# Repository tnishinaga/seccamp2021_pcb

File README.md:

# ft2232_jtag_tap

# KiCad version

5.1.8

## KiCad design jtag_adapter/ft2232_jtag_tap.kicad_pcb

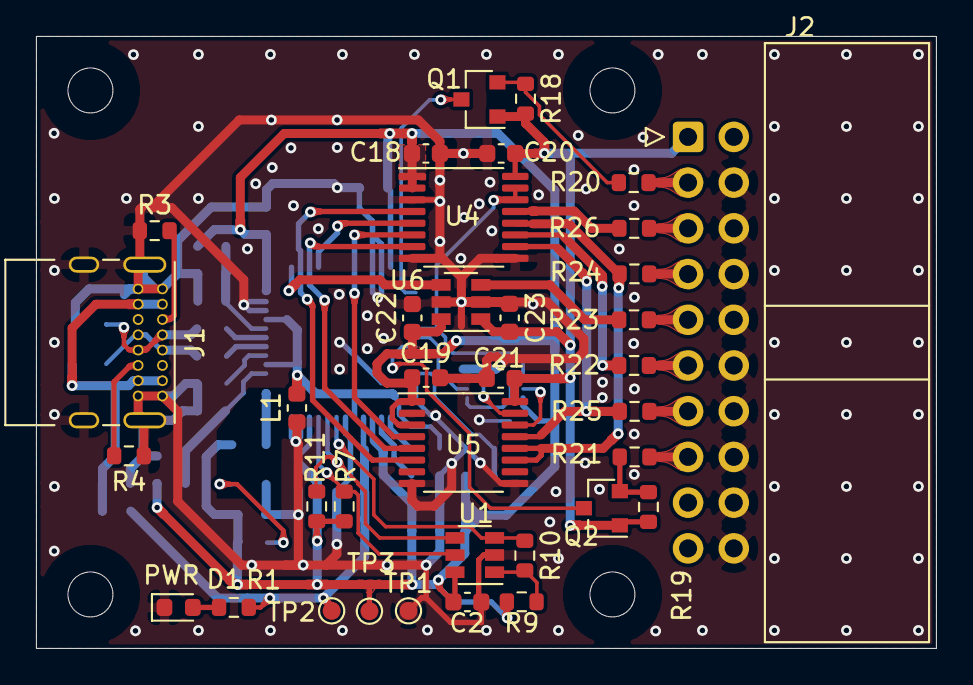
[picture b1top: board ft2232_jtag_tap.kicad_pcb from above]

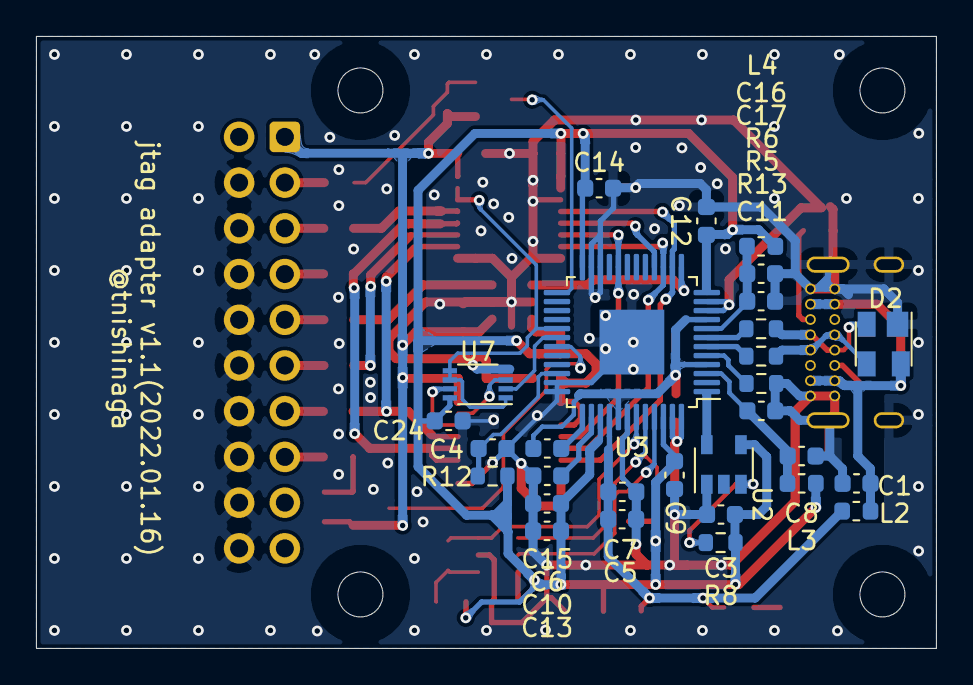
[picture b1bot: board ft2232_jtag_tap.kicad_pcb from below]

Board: 2 copper layers, 50.0 x 34.0 mm, 69 parts (29 on the bottom side), 50 nets.

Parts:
C1: 0.01uF; C_0603_1608Metric
C2: N.F./0.1uF; C_0603_1608Metric
C3, C4, C6, C7, C9, C11, C12, C13, C14, C15, C17, C18, C19, C20, C21, C22, C23, C24: 0.1uF; C_0603_1608Metric
C5, C8, C10, C16: 4.7uF; C_0603_1608Metric
D1: PWR_LED; LED_0603_1608Metric
D2: PRTR5V0U2X; SOT-143
H1, H2, H3, H4: MountingHole; MountingHole_2.5mm
J1: USB_C_Receptacle_USB2.0; USB_C_Receptacle_GCT_USB4085
J2: Conn_ARM_JTAG_SWD_20; IDC-Header_2x10_P2.54mm_Horizontal
L1, L2, L3, L4: 600R/0.5A; L_0603_1608Metric
Q1, Q2: BSS138; SOT-23
R1: 1k; R_0603_1608Metric
R3, R4: 5.1k; R_0603_1608Metric
R5, R6, R20, R21, R22, R23, R24, R25, R26: 0; R_0603_1608Metric
R7, R9, R11: N.F./10k; R_0603_1608Metric
R8, R18, R19: 10k; R_0603_1608Metric
R10: N.F./2k; R_0603_1608Metric
R12: 100k; R_0603_1608Metric
R13: 12k/1%; R_0603_1608Metric
TP1: GND; TestPoint_Pad_D1.0mm
TP2: +5V; TestPoint_Pad_D1.0mm
TP3: +3.3V; TestPoint_Pad_D1.0mm
U1: N.F./93AA56BT-I/OT; SOT-23-6
U2: SIT2001B; SOT-23-5
U3: FT232HL; LQFP-48-1EP_7x7mm_P0.5mm_EP3.6x3.6mm
U4, U5: SN74AXCH4T245PW; TSSOP-16_4.4x5mm_P0.65mm
U6: SN74AXCH1T45DBVR; SOT-23-6
U7: SN74LVC2G00DCUT; VSSOP-8_2.3x2mm_P0.5mm

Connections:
+1V8: C6.1, U3.38
+3V3: C2.1, C3.1, C9.1, C10.1, C12.1, C13.1, C14.1, C18.1, C19.1, C22.1, C24.2, L3.2, L4.2, R7.2, R8.2, R9.2, R11.2, R12.2, TP3.1, U1.6, U2.4, U3.12, U3.24, U3.39, U3.46, U4.1, U4.2, U5.1, U5.3, U6.6, U7.8
+5V: C5.1, C7.1, L2.1, R1.2, TP2.1, U3.40
/ft232hl/EEPROM_CLK: R11.1, U1.4, U3.44
/ft232hl/EEPROM_CS: R7.1, U1.5, U3.45
/ft232hl/EEPROM_DATA: R10.1, U1.3, U3.43
/ft232hl/JTAG_RTCK: U3.20, U4.6, U5.4
/ft232hl/JTAG_TCK: U3.13, U6.4
/ft232hl/JTAG_TDI: U3.14, U4.4, U5.6
/ft232hl/JTAG_TDO: U3.15, U4.7, U5.5
/ft232hl/JTAG_TMS: U3.16, U4.5
/ft232hl/JTAG_nSRST: Q2.3, U3.31
/ft232hl/JTAG_nTRST: Q1.3, U3.25
/ft232hl/SWDIO_OE: U3.30, U7.2
/ft232hl/SWD_EN: U3.29, U4.14, U4.15, U7.1, U7.5, U7.6
/ft232hl/USB_D+: R6.1, U3.7
/ft232hl/USB_D-: R5.1, U3.6
/ft232hl/VCCA: C15.1, U3.37
/ft232hl/VPHY: C8.1, C11.1, L3.1, U3.3
/ft232hl/VPLL: C16.1, C17.1, L4.1, U3.8
/ft232hl/XCSI: U2.5, U3.1
/ft232hl/~RESET: C4.1, R12.1, U3.34
/jtag/CONN_RTCK: J2.11, R22.2
/jtag/CONN_TCK: J2.9, R23.2
/jtag/CONN_TDI: J2.5, R26.2
/jtag/CONN_TDO: J2.13, R25.2
/jtag/CONN_TMS: J2.7, R24.2
/jtag/CONN_~SRST: J2.15, R21.2
/jtag/CONN_~TRST: J2.3, R20.2
/jtag/RTCK: R22.1, U4.11
/jtag/TCK_SWDCLK: R23.1, U6.3
/jtag/TDI: R26.1, U4.13
/jtag/TDO_SWO: R25.1, U4.10, U5.13
/jtag/TMS_SWDIO: R24.1, U4.12, U5.11, U5.12
/jtag/VTREF: C20.2, C21.2, C23.2, J2.1, Q1.1, Q2.1, R18.2, R19.2, U4.16, U5.16, U6.1
/jtag/~SRST: Q2.2, R19.1, R21.1
/jtag/~SWD_EN: U5.15, U7.3
/jtag/~SWD_OE: U5.14, U7.7
/jtag/~TRST: Q1.2, R18.1, R20.1
/usb/D+: D2.2, J1.A6, J1.B6, R6.2
/usb/D-: D2.3, J1.A7, J1.B7, R5.2
/usb/VBUS: C1.1, D2.4, J1.A4, J1.A9, J1.B4, J1.B9, L2.2
GND: C1.2, C2.2, C3.2, C4.2, C5.2, C6.2, C7.2, C8.2, C9.2, C10.2, C11.2, C12.2, C13.2, C14.2, C16.2, C17.2, C18.2, C19.2, C20.1, C21.1, C22.2, C23.1, C24.1, D1.1, D2.1, J1.A1, J1.A12, J1.B1, J1.B12, J1.S1, J2.4, J2.6, J2.8, J2.10, J2.12, J2.14, J2.16, J2.18, J2.20, L1.1, R3.1, R4.1, R13.2, TP1.1, U1.2, U2.1, U3.10, U3.11, U3.22, U3.23, U3.35, U3.36, U3.42, U3.47, U3.48, U3.49, U4.3, U4.8, U4.9, U5.2, U5.8, U5.9, U6.2, U6.5, U7.4
GNDA: C15.2, L1.2, U3.4, U3.9, U3.41
unnamed: D1.2, R1.1
unnamed: J1.A5, R3.2
unnamed: J1.B5, R4.2
unnamed: R8.1, U2.3
unnamed: R9.1, R10.2, U1.1
unnamed: R13.1, U3.5

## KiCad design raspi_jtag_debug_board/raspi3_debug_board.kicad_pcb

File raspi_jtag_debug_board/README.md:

# raspi_development_expand_board
Development board that expands JTAG, UART, I2C, PWM ports for Raspberry Pi

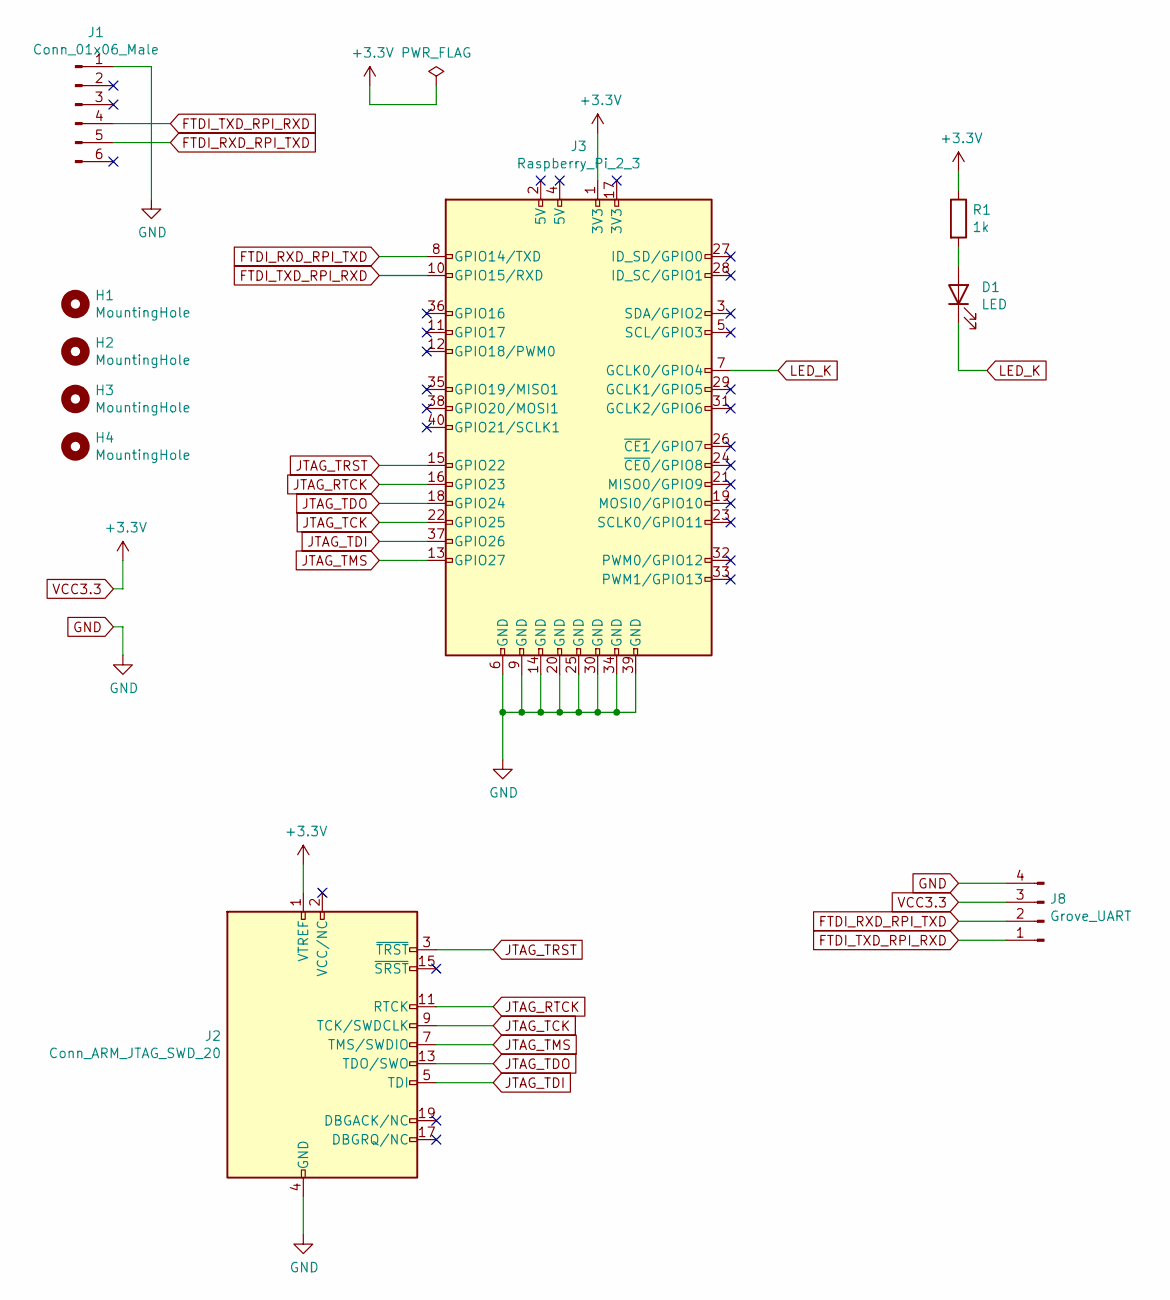
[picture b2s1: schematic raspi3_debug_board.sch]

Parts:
D1: LED; LED_D3.0mm
H1, H2, H3, H4: MountingHole; MountingHole_2.7mm_M2.5
J1: Conn_01x06_Male; PinHeader_1x06_P2.54mm_Horizontal
J2: Conn_ARM_JTAG_SWD_20; Multicomp_MC9A22-2034_2x10_P2.54mm_Horizontal
J3: Raspberry_Pi_2_3; PinSocket_2x20_P2.54mm_Vertical
J8: Grove_UART; NS-Tech_Grove_1x04_P2mm_Vertical
R1: 1k; R_Axial_DIN0207_L6.3mm_D2.5mm_P10.16mm_Horizontal

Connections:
FTDI_RXD_RPI_TXD: J1.5, J3.8 (GPIO14/TXD), J8.2
FTDI_TXD_RPI_RXD: J1.4, J3.10 (GPIO15/RXD), J8.1
GND: J1.1, J2.4 (GND), J2.6 (GND), J2.8 (GND), J2.10 (GND), J2.12 (GND), J2.14 (GND), J2.16 (GND), J2.18 (GND), J2.20 (GND), J3.6 (GND), J3.9 (GND), J3.14 (GND), J3.20 (GND), J3.25 (GND), J3.30 (GND), J3.34 (GND), J3.39 (GND), J8.4
JTAG_RTCK: J2.11 (RTCK), J3.16 (GPIO23)
JTAG_TCK: J2.9 (TCK/SWDCLK), J3.22 (GPIO25)
JTAG_TDI: J2.5 (TDI), J3.37 (GPIO26)
JTAG_TDO: J2.13 (TDO/SWO), J3.18 (GPIO24)
JTAG_TMS: J2.7 (TMS/SWDIO), J3.13 (GPIO27)
JTAG_TRST: J2.3 (~TRST~), J3.15 (GPIO22)
LED_K: D1.1 (K), J3.7 (GCLK0/GPIO4)
unnamed: D1.2 (A), R1.2
VCC3.3: J2.1 (VTREF), J3.1 (3V3), J8.3, R1.1

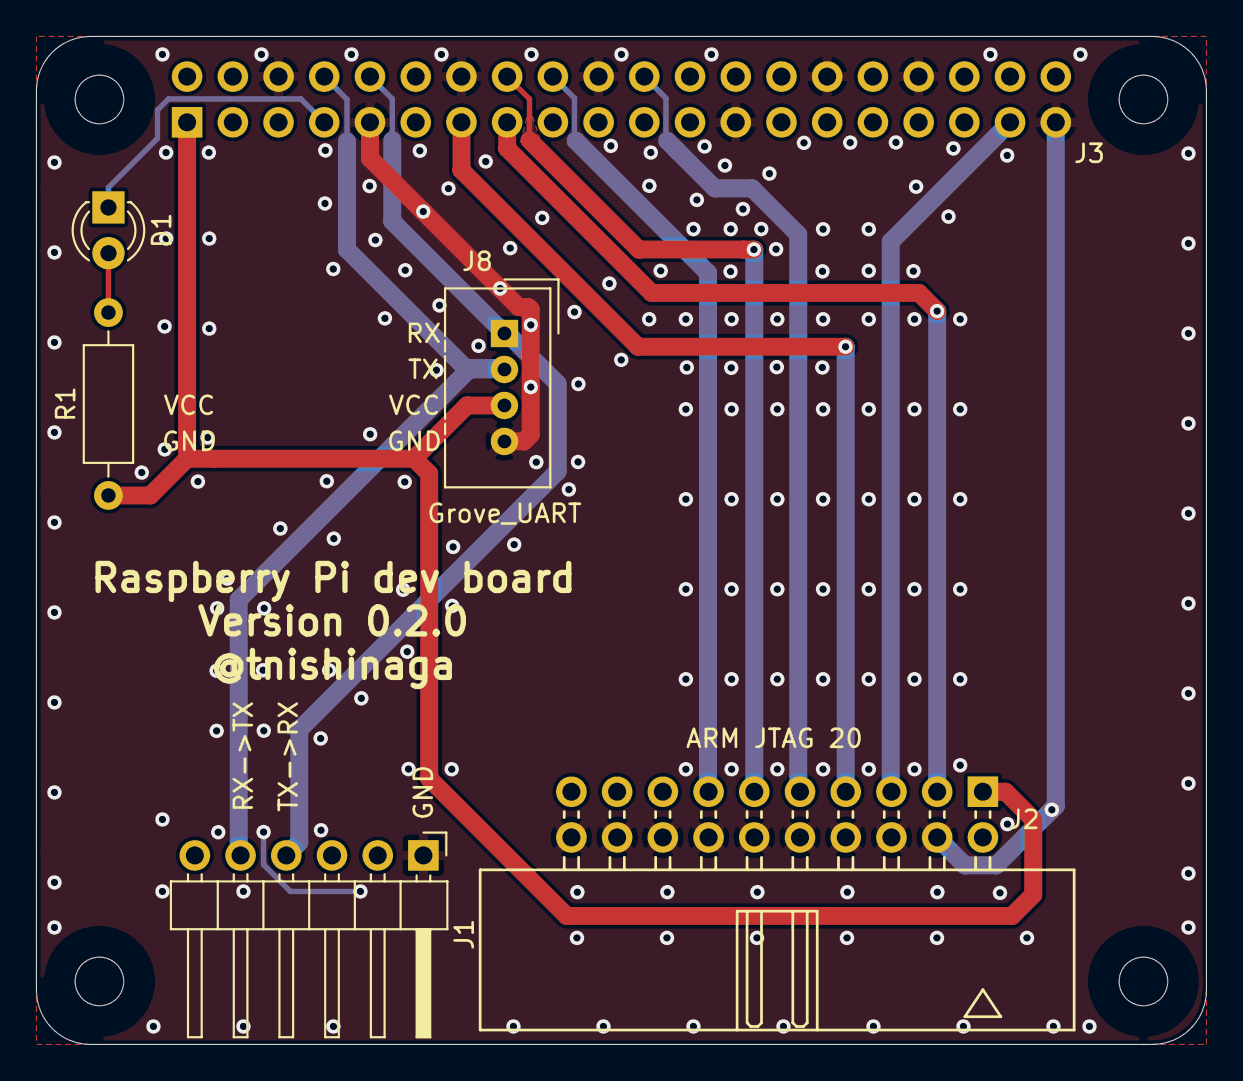
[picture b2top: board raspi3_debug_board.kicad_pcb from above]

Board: 2 copper layers, 65.0 x 56.0 mm, 10 parts (1 on the bottom side), 12 nets.

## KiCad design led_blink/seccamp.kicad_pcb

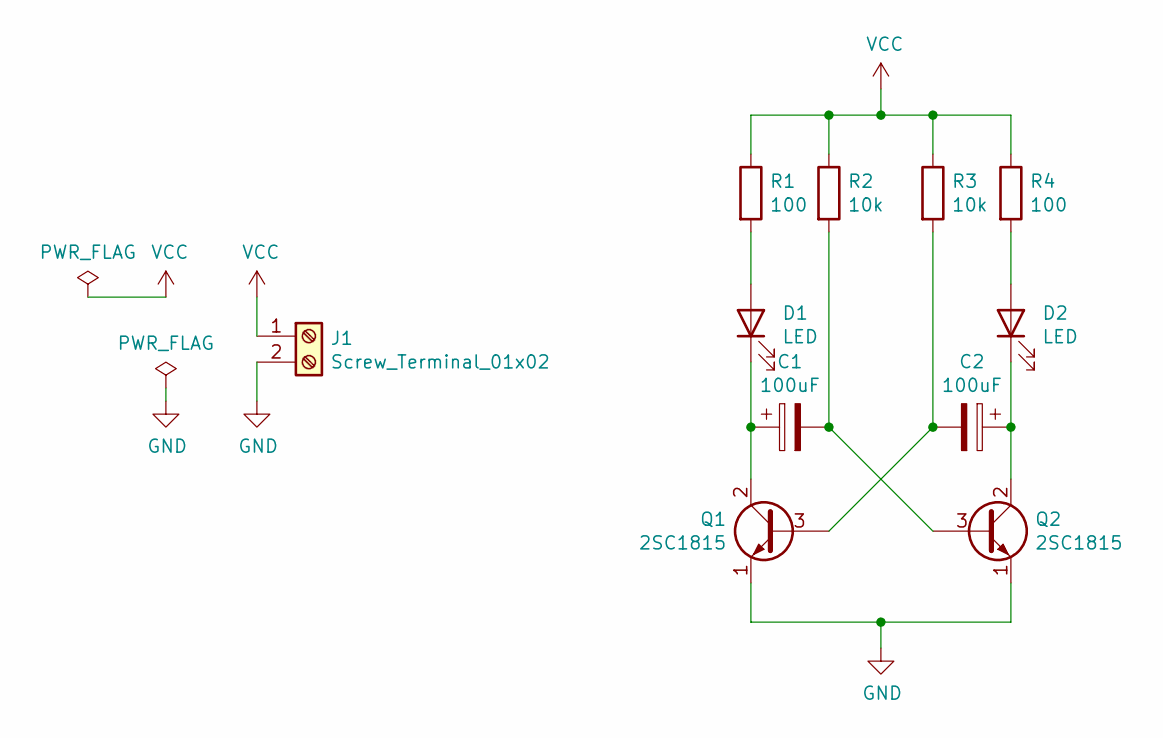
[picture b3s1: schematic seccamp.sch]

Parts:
C1, C2: 100uF; CP_Radial_D5.0mm_P2.50mm
D1, D2: LED; LED_D3.0mm
J1: Screw_Terminal_01x02; TerminalBlock_bornier-2_P5.08mm
Q1, Q2: 2SC1815; TO-92
R1, R4: 100; R_Axial_DIN0207_L6.3mm_D2.5mm_P10.16mm_Horizontal
R2, R3: 10k; R_Axial_DIN0207_L6.3mm_D2.5mm_P10.16mm_Horizontal

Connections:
GND: J1.2, Q1.1 (E), Q2.1 (E)
unnamed: C1.1, D1.1 (K), Q1.2 (C)
unnamed: C1.2, Q2.3 (B), R2.2
unnamed: C2.1, D2.1 (K), Q2.2 (C)
unnamed: C2.2, Q1.3 (B), R3.2
unnamed: D1.2 (A), R1.2
unnamed: D2.2 (A), R4.2
VCC: J1.1, R1.1, R2.1, R3.1, R4.1

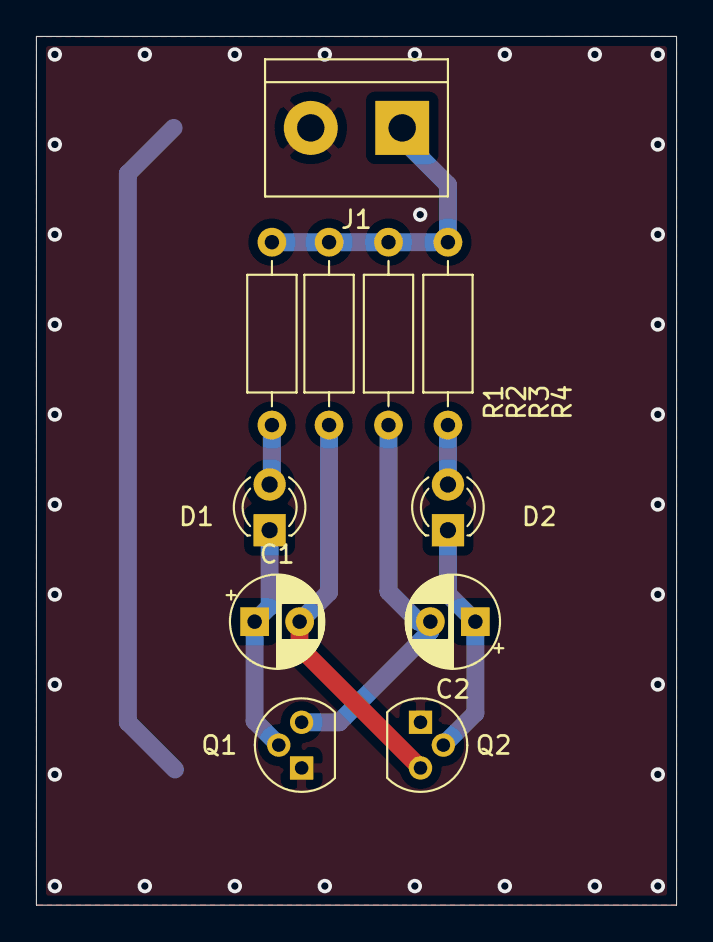
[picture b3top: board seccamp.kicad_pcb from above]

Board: 2 copper layers, 35.6 x 48.3 mm, 11 parts (0 on the bottom side), 8 nets.

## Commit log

2021-07-04 release v0.1
2021-07-04 cleanup
2021-07-17 v0.2に改修
2021-07-17 Add panelize
2021-07-18 v0.2 発注
2021-07-18 Add ltspice file
2021-08-05 fix pi3 config
2021-08-11 コンデンサをCからCPに変更
2021-08-13 fix SRST/TRST and remove unnecessary files
2021-08-13 fix gnd
2021-08-22 秋月FT232HLモジュールを使った回路を追加
2021-08-22 wip: 回路図の改善とレベル変換ICの追加
2021-09-04 v1.0 基板発注
2021-09-24 wip: remove JTAG_EN pin
2022-03-15 wip: stash
